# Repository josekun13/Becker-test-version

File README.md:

# Becker-test-version
The purpose of this robot is to test and develop human-robot interaction
applications, also control models for non-linear systems.
## Introduction
R.Becker :smiley_cat: is an inverted pendulum on two wheels, the idea of
this kind of design is the dynamically stable robots are inherently safe 
to work in human environments.

*Inverted pendulum on two wheels*

The inverted pendulum is the simplest version of a dynamically stable 
robot.

The operation of Becker consist in an IMU that measure the inclination
angle, a control module and two DC. motors that correct the
disturbances.

## Structure
The shape of the robot consist in a base with a column in the middle, in 
the base are two axis that connect the wheels with the motors, the axis
are support by two ball bearings each one.

### Characteristics
* Column
is a 20X20 aluminium IPS with one meter length.
* Base
is an aluminium plate of 1/4 inches (6.35mm) with a size of 20cm x 60cm.
* Ball bearing base
is a square print in PLA with a density of 75% and a hexagonal fill 
pattern, it fits a ball bearing 1/4" x 5/8".
* Axis
they are made of stainless steel with a length  of 12cm.

*3d models and planes are in the *
 
## Electronics
Electronic system is composed by three main parts:
* Power Source
* Control Unit
* Power Stage

### Power Source   :battery:
Becker is powered by two batteries, one for the control system and the 
other for the motors. this is in order to avoid interference caused by
the motors in the control system.

The control system battery have a charge capacity of 10,000 mAh with
and output of 5V 2A, the battery use an USB port to as terminal.

The motors battery is a 5000mAh LiPo with an output of 11.1v and a 
maximum discharge rate of 50A.

### Control Unit  :computer:
Becker use a Raspberry Pi 2B+ as CPU, IMU are communicated using I²C, 
Encoders, PWM and direction pins of the motor drivers are conected to 
GPIOs of the CPU (throught optocouplers).

### Power Stage  :low_brightness:
It's made of two parts, the first is the motor drivers, and the second 
is an optocoupler array.

Motor drivers (VHN5019) function is to provide enough curren to motors,
their logic circuit work at 5V, they are supply by a buck type source.

Optocoupler array function is to isolate the motor circuit and the 
control circuit.

*Electronic diagrams are in the .*

## Simulation
Becker dynamic model simulation was made using matlab.

### Dynamic Model
The dynamic model of becker is an inverted pendulum considering that 
it's behavior is linear near vertical stability point.

The model equations and space state analysis are explained in detail in
the thesis "Desarrollo de un robot de dos ruedas dinámicamente estable"
the document is in the .

Dynamic model diagram in SimuLink is as follows.

### Control System 
The control system is an modification of ac classic PID controller,
this version only use the integrative part in one of the inputs, is 
called PD+I.

In simulation the control was robust enough to compensate perturbances 
of 30° in inclination. The experiments in with the prototipe show
an enormous diference, the real robot can compensare only 4° 
disturbances, this fluctuation is because the suposition of a linear
behaivor.

*Control model and dynamic model simulations are in 
 .*

## R.O.S.
Becker use R.O.S. Indigo, the node diagram is as follow.

*The R.O.S. workspace is in the folder .*

### Encodernode
This node read the signals of motor's encoders and calculate the angle 
of each motor with a sample rate of 10,700 times per second.

### Imunode
Imunode obtains the measurements of the 3 axis accelerometer and 
gyroscope and use a complementary filter to calculate the angle. 

### Controlnode
The controlnode is the main node of Becker, it read the messages of the
encodernode and imunode asynchronously, calculate the derivative and
integrative values and generate the control signal for each wheel.

### Motornode
Motornode generate the PWM and direction signals for the motor drivers.

## Possible Improvements
The next list shows improvements that help the Becker's performance:

* An adaptative control system.
* Externar microcontroller to generate PWM signals.
* A new CPU version.

These points are better explained in the .

## Videos
In this links are some videos of Becker working.

[Becker video](https://youtu.be/0lUVMNjOlis).

## Operation
These is the boot sequence of Becker:

1. Put Becker in vertical position, ( this is because the IMU need this
angle as reference).

1. Start the roscore (note: the next steps need to be made in as super
user).

1. Start the encodernode.

1. Start the imunode.

1. Start the motornode.

1. Start the controlnode.

1. Release Becker  :smirk_cat: .

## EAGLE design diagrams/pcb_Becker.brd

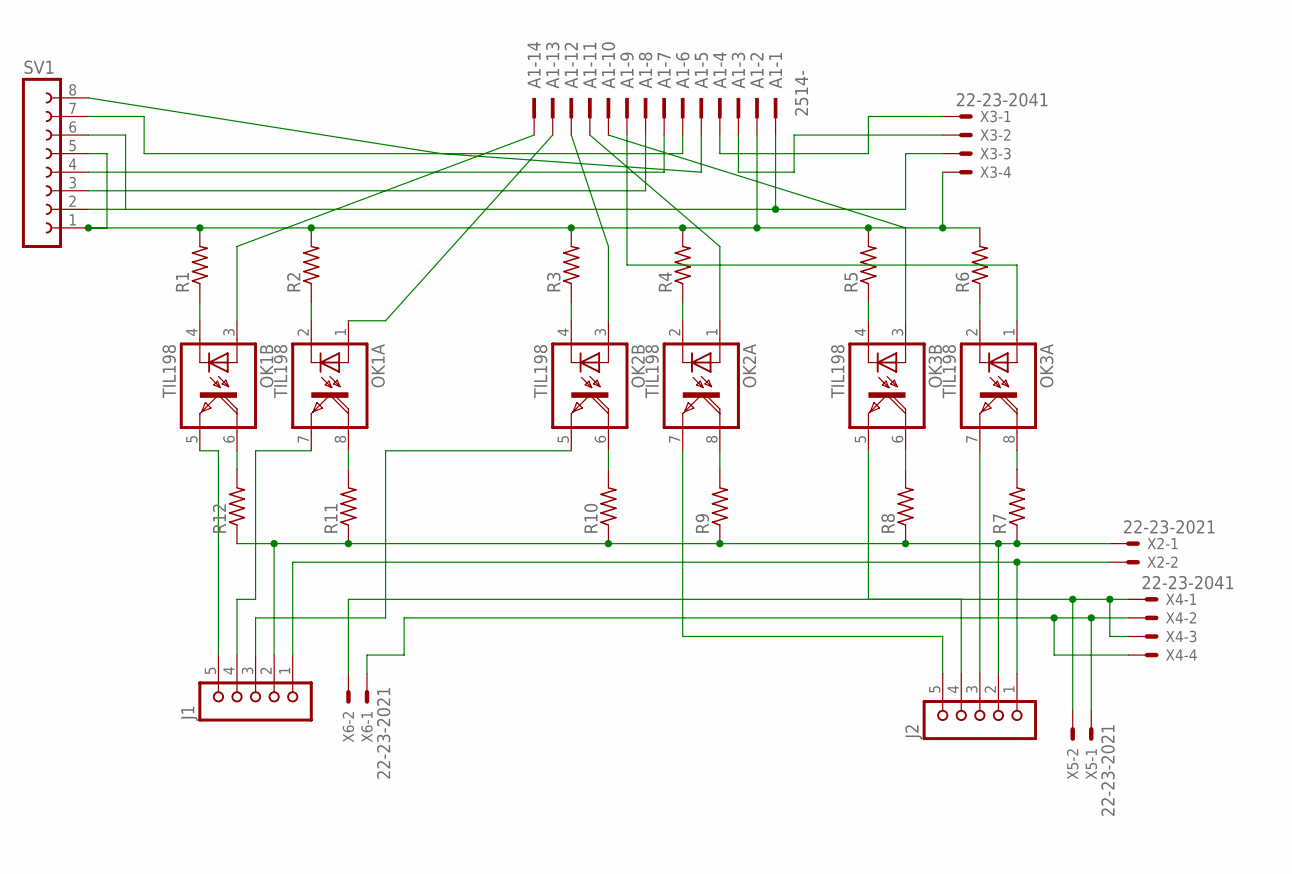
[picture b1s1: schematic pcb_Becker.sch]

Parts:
A1: 2514-; PAK100/2500-14
J1, J2: JU05
OK1, OK2, OK3: TIL198; DIL08
R1, R2, R3, R4, R5, R6, R7, R8, R9, R10, R11, R12: R-US_0207/10; 0207/10
SV1: FE08-1; FE08
X2, X5, X6: 22-23-2021
X3, X4: 22-23-2041

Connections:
unnamed: OK1.4 (C), R1.1
unnamed: OK1.2 (C), R2.1
unnamed: OK2.4 (C), R3.1
unnamed: OK2.2 (C), R4.1
unnamed: OK3.4 (C), R5.1
unnamed: OK3.2 (C), R6.1
unnamed: OK3.8 (COL), R7.2
unnamed: OK3.6 (COL), R8.2
unnamed: OK2.8 (COL), R9.2
unnamed: OK2.6 (COL), R10.2
unnamed: OK1.8 (COL), R11.2
unnamed: OK1.6 (COL), R12.2
unnamed: A1.14, OK1.3 (A)
unnamed: A1.13, OK1.1 (A)
unnamed: A1.12, OK2.3 (A)
unnamed: A1.11, OK2.1 (A)
unnamed: A1.10, OK3.3 (A)
unnamed: A1.9, OK3.1 (A)
unnamed: A1.2, R1.2, R2.2, R3.2, R4.2, R5.2, R6.2, SV1.1, SV1.5, X3.4
unnamed: J1.5, OK1.5 (EMI)
unnamed: J1.4, OK1.7 (EMI)
unnamed: J1.3, OK2.5 (EMI)
unnamed: J2.5, OK2.7 (EMI)
unnamed: J2.4, OK3.5 (EMI)
unnamed: J2.3, OK3.7 (EMI)
unnamed: J1.2, J2.2, R7.1, R8.1, R9.1, R10.1, R11.1, R12.1, X2.1
unnamed: J1.1, J2.1, X2.2
unnamed: A1.1, SV1.2, SV1.6, X3.3
unnamed: A1.8, SV1.3
unnamed: A1.7, SV1.4
unnamed: A1.6, SV1.7
unnamed: A1.5, SV1.8
unnamed: A1.4, X3.1
unnamed: A1.3, X3.2
unnamed: X4.1, X4.3, X5.2, X6.2
unnamed: X4.2, X4.4, X5.1, X6.1

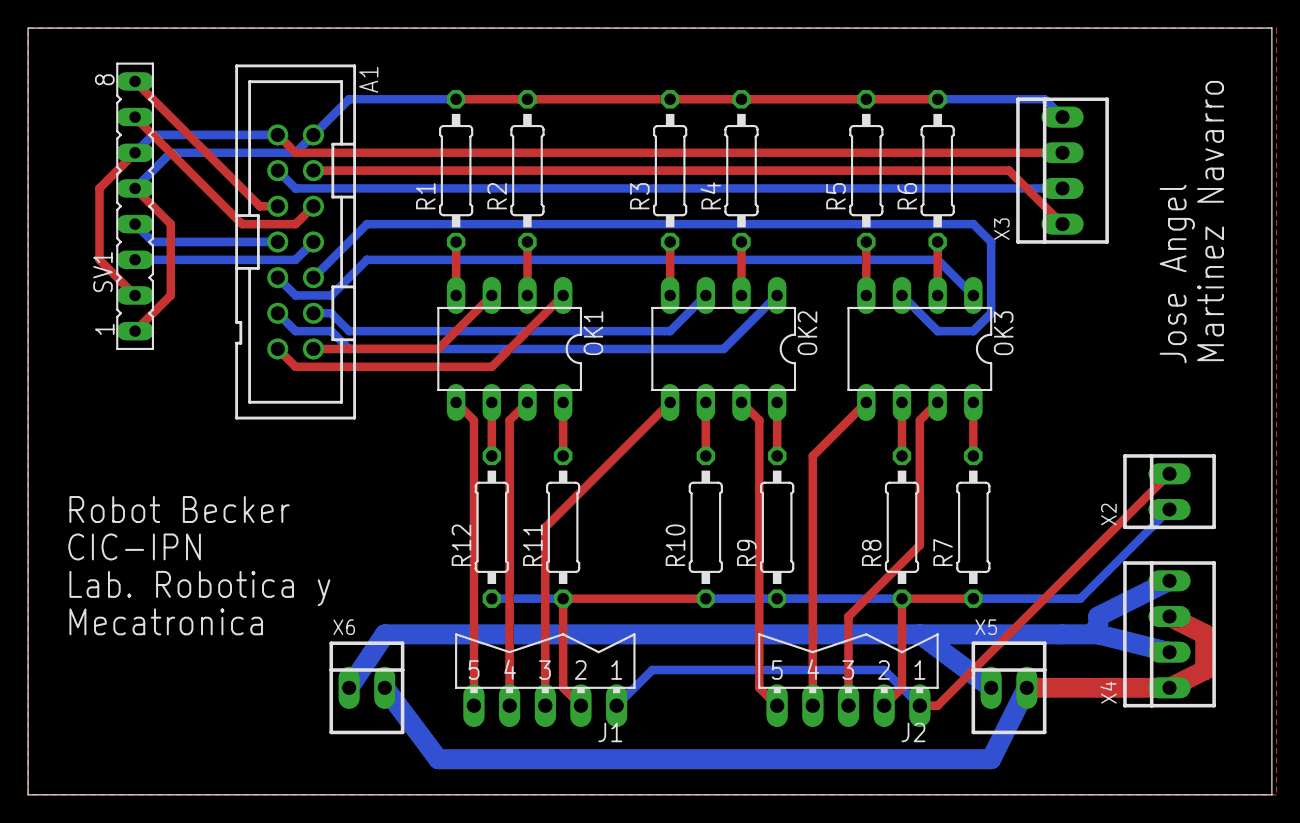
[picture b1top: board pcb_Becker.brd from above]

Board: 2 copper layers, 88.6 x 54.6 mm, 24 parts (0 on the bottom side), 36 nets.

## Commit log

2016-10-07 modified: README.md new file: catkin_ws/.catkin_workspace new file: catkin_ws/build/.built_by new file: catkin_ws/build/CATKIN_IGNORE new file: catkin_ws/build/CMakeCache.txt new file: catkin_ws/buil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
2018-01-17 Becker test version Actualizacion falta limpiar
2018-02-09 New form to readme.md
2018-02-09 cambio en los textos
2018-02-12 Cambios al texto
2018-02-13 Estrctura de la portada
2018-02-13 Add emoji
2018-02-13 emoji correction
2018-02-13 Image folder added
2018-02-13 imagen actualizada
2018-02-14 Introduction Ready
2018-02-14 resize
2018-02-14 resize 3
2018-02-14 html test
2018-02-14 html success
2018-02-14 new test images
2018-02-14 readyy
2018-02-15 Structure section
2018-02-15 list
2018-02-15 sound
2018-02-15 folder added
2018-02-16 models folder
2018-02-16 rename
2018-02-16 textos
2018-02-16 text
2018-02-16 text2
2018-02-16 Electronic
2018-02-16 Imagen
2018-02-19 Diagram folder Added
2018-02-19 documents added
2018-02-19 pd+i
2018-02-22 Simulations
2018-02-22 ros diagram
2018-02-22 image change
2018-02-22 nodes
2018-02-22 videos
2018-02-22 correction
2018-02-22 ready to check
2018-02-22 lista
2018-02-27 text correction
2018-02-27 tect changes
2018-02-27 ws link add
2018-02-27 final version
